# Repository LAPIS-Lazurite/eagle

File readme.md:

# notice of usage
this repository is for eagle library and SCH/PCB of Lazurite mini series.
Currently all files are not confirmed yet because PCB is under development. Please use it with your confirmation.

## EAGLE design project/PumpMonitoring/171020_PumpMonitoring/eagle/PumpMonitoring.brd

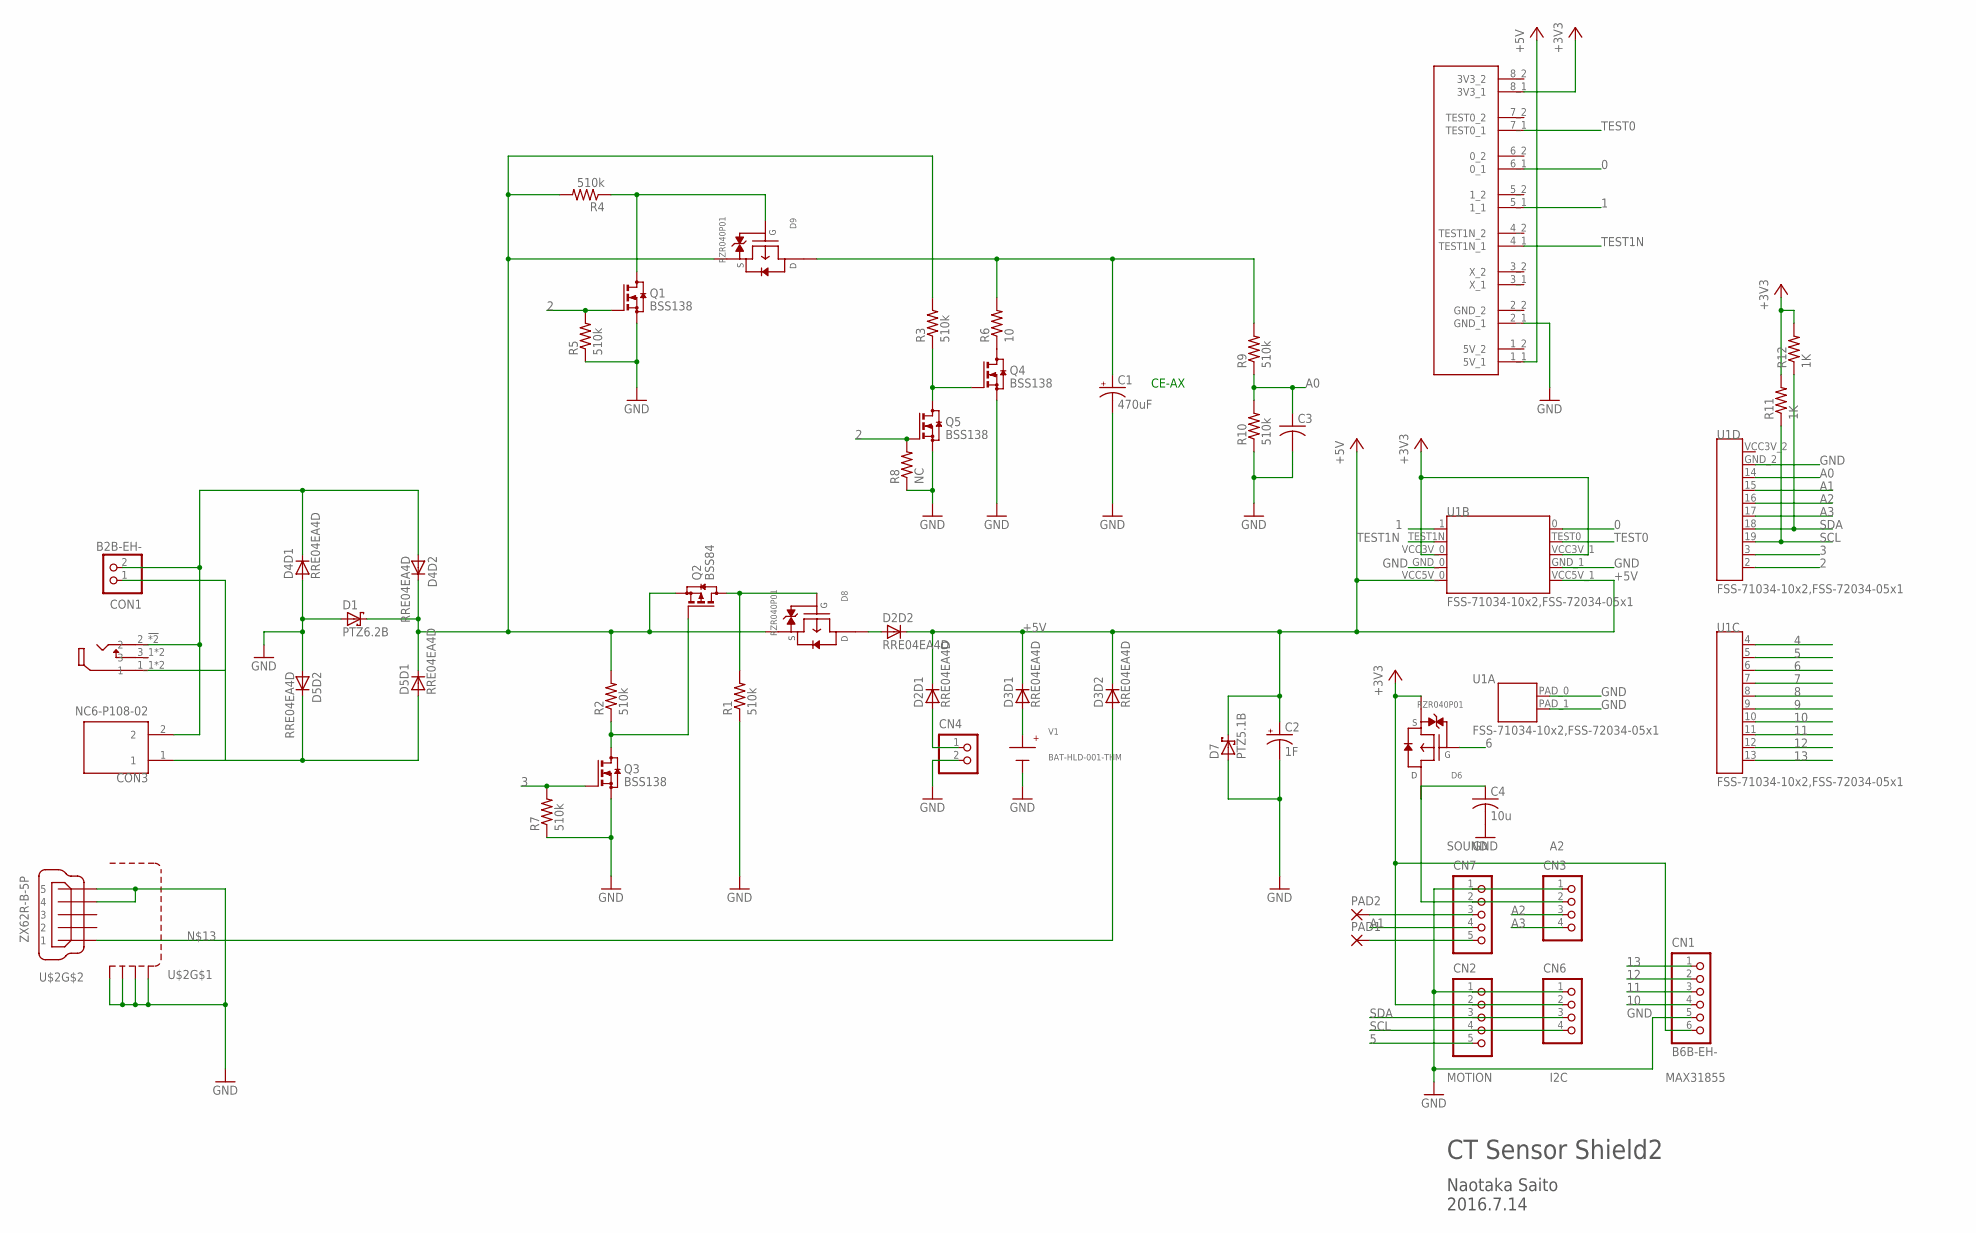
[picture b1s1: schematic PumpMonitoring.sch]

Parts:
C1: 470uF; E5-10,5
C2: 1F; E5-20
C3: C-USC0603; C0603
C4: 10u; C1206
CN1: B6B-EH-; B6B-EH
CN2, CN7: B5B-PH-K-S
CN3, CN6: B4B-PH-K-S
CN4: B2B-PH-K-S
CON1: B2B-EH-; B2B-EH
CON2: MJ-3536N
CON3: NC6-P108-02; 2PIN
D1: PTZ6.2B; DO214AC
D2, D3, D4, D5: RRE04EA4D; TSMD5
D6, D8, D9: RZR040P01; TSMT3
D7: PTZ5.1B; DO214AC
PAD1, PAD2: 1,6/0,9
Q1, Q3, Q4, Q5: BSS138; SOT23
Q2: BSS84; SOT23
R1, R2, R3, R4, R5, R7, R9, R10: 510k; R0603
R6: 10; EZP
R8: NC; R0603
R11, R12: 1K; R0603
U1: FSS-71034-10x2,FSS-72034-05x1; LAZURITE920J
U$1: XB-1-X
U$2: ZX62R-B-5P
V1: BAT-HLD-001-THM; CR2032

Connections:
0: U1.0, U$1.6_1 (0_1)
1: U1.1, U$1.5_1 (1_1)
2: Q1.1 (G), Q5.1 (G), R5.2, R8.2, U1.2
3: Q3.1 (G), R7.2, U1.3
4: U1.4
5: CN2.5, U1.5
6: D6.1 (G), U1.6
7: U1.7
8: U1.8
9: U1.9
10: CN1.4, U1.10
11: CN1.3, U1.11
12: CN1.2, U1.12
13: CN1.1, U1.13
+3V3: CN1.6, CN2.2, CN6.2, D6.2 (S), R11.2, R12.2, U1.VCC3V_0, U1.VCC3V_1, U$1.8_1 (3V3_1)
+5V: C2.+, D2.4 (C), D2.5 (C), D3.4 (C), D3.5 (C), D7.C, U1.VCC5V_0, U1.VCC5V_1, U$1.1_1 (5V_1)
A0: C3.1, R9.1, R10.2, U1.14
A1: CN7.4, U1.15
A2: CN3.3, U1.16
A3: CN3.4, U1.17
GND: C1.-, C2.-, C3.2, C4.2, CN1.5, CN2.1, CN3.1, CN4.2, CN6.1, CN7.1, D1.A, D4.1 (A), D5.3 (A), D7.A, Q1.2 (S), Q3.2 (S), Q4.2 (S), Q5.2 (S), R1.1, R5.1, R7.1, R8.1, R10.1, U1.GND_0, U1.GND_1, U1.GND_2, U1.PAD_0, U1.PAD_1, U$1.2_1 (GND_1), U$2.4, U$2.5, U$2.M1 (S1), U$2.M2 (S2), U$2.M3 (S3), U$2.M4 (S4), V1.GND
I+: CON1.2, CON2.2_2 (2), CON2.2_! (2), CON3.2, D4.3 (A), D4.5 (C)
I-: CON1.1, CON2.1_1 (1), CON2.1_2 (1), CON3.1, D5.1 (A), D5.4 (C)
IOUT: D1.C, D4.4 (C), D5.5 (C), D8.2 (S), D9.2 (S), Q2.2 (S), R2.2, R3.2, R4.2
unnamed: D8.1 (G), Q2.3 (D), R1.2
unnamed: D3.1 (A), V1.VDD1 (VDD), V1.VDD2 (VDD), V1.VDD3 (VDD), V1.VDD4 (VDD)
unnamed: CN4.1, D2.1 (A)
unnamed: C4.1, CN3.2, CN7.2, D6.3 (D)
unnamed: Q2.1 (G), Q3.3 (D), R2.1
unnamed: CN7.5, PAD1.1
unnamed: D9.1 (G), Q1.3 (D), R4.1
unnamed: CN7.3, PAD2.1
unnamed: Q4.3 (D), R6.1
unnamed: C1.+, D9.3 (D), R6.2, R9.2
unnamed: Q4.1 (G), Q5.3 (D), R3.1
unnamed: D2.3 (A), D8.3 (D)
unnamed: D3.3 (A), U$2.1
SCL: CN2.4, CN6.4, R11.1, U1.19
SDA: CN2.3, CN6.3, R12.1, U1.18
TEST0: U1.TEST0, U$1.7_1 (TEST0_1)
TEST1N: U1.TEST1N, U$1.4_1 (TEST1N_1)

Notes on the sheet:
CE-AX
CT Sensor Shield2
Naotaka Saito 2016.7.14
MOTION
SOUND
I2C
MAX31855

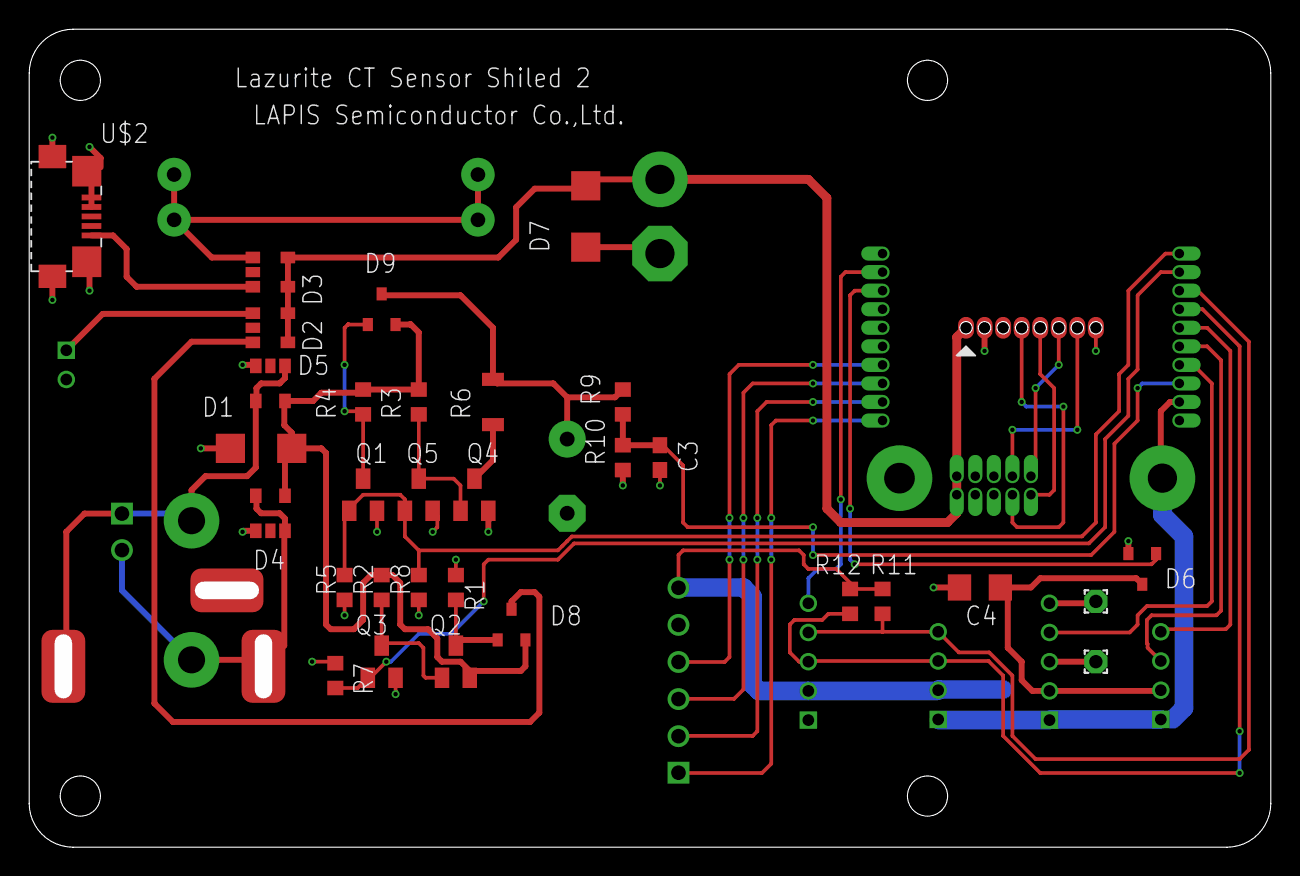
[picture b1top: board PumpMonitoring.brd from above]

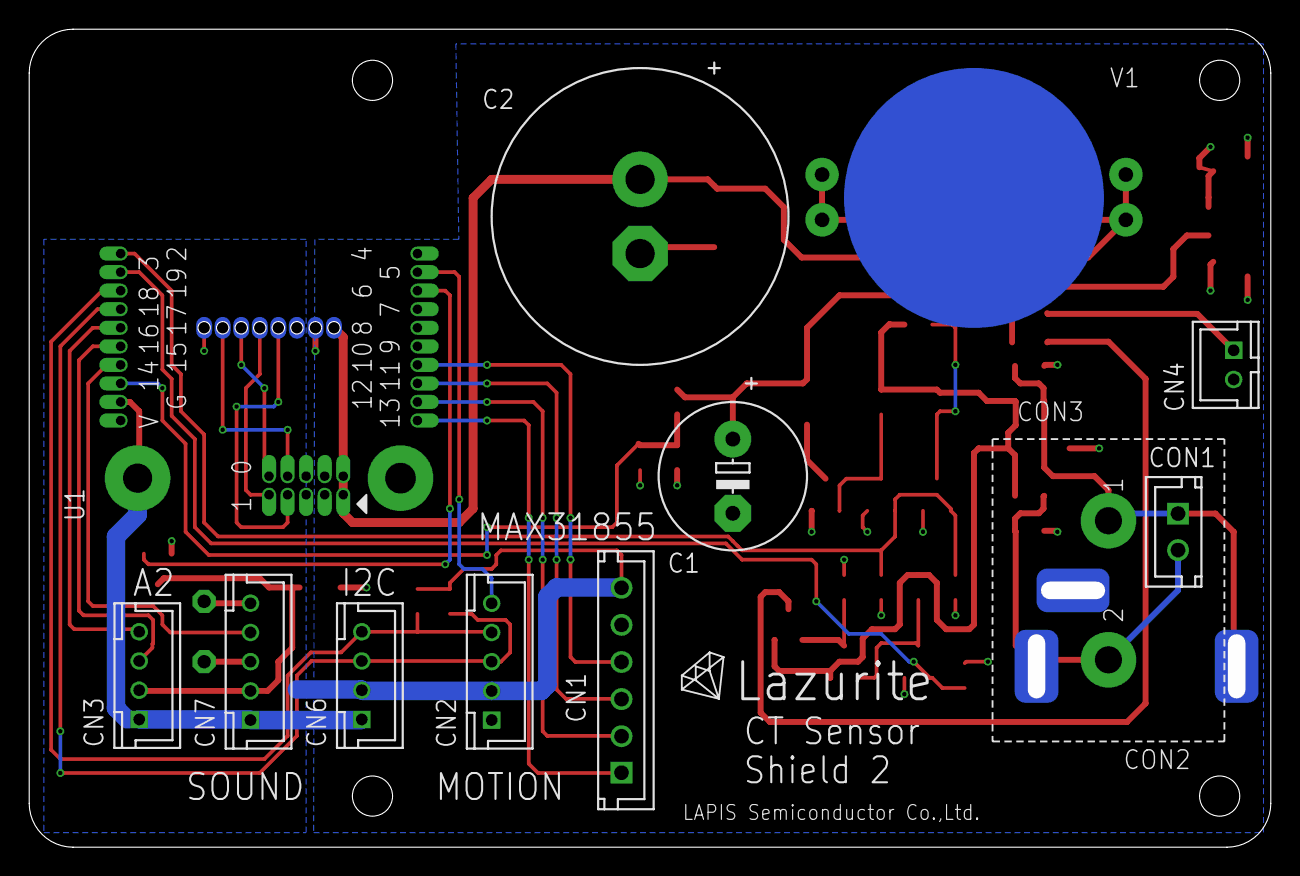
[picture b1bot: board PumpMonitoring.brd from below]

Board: 4 copper layers, 83.8 x 54.8 mm, 46 parts (14 on the bottom side), 37 nets.

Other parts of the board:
U$3: LOGO

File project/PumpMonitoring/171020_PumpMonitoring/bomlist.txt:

Partlist

Exported from PumpMonitoring.brd at 2017/10/20 9:58

EAGLE Version 7.6.0 Copyright (c) 1988-2016 CadSoft

Assembly variant: 

Part     Value                         Package      Library                 Position (mm)         Orientation

C1       470uF                         E5-10,5      rcl                     (36.83 25.4)          MR270
C2       1F                            E5-20        rcl                     (43.18 43.18)         MR270
C3                                     C0603        rcl                     (43.18 26.67)         R270
C4       10u                           C1206        rcl                     (65.0875 17.78)       R180
CN1      B6B-EH-                       B6B-EH       jst-ph                  (44.45 11.43)         MR90
CN2                                    B5B-PH-K-S   jst-ph                  (53.34 12.7)          MR90
CN3                                    B4B-PH-K-S   jst-ph                  (77.47 11.7475)       MR90
CN4                                    B2B-PH-K-S   jst-ph                  (2.54 33.02)          MR270
CN6                                    B4B-PH-K-S   jst-ph                  (62.23 11.7475)       MR90
CN7                                    B5B-PH-K-S   jst-ph                  (69.85 12.7)          MR90
CON1     B2B-EH-                       B2B-EH       jst-ph                  (6.35 21.59)          MR270
CON2     MJ-3536N                      MJ-3536N     mouser                  (7.9375 12.3825)      MR180
CON3     NC6-P108-02                   2PIN         lz-shield               (19.05 27.94)         MR270
D1       PTZ6.2B                       DO214AC      rohm2                   (15.875 27.305)       R0
D2       RRE04EA4D                     TSMD5        rohm2                   (16.51 35.56)         R270
D3       RRE04EA4D                     TSMD5        rohm2                   (16.51 39.37)         R270
D4       RRE04EA4D                     TSMD5        rohm2                   (16.51 22.86)         R0
D5       RRE04EA4D                     TSMD5        rohm2                   (16.51 31.75)         R180
D6       RZR040P01                     TSMT3        rohm2                   (76.2 19.05)          R180
D7       PTZ5.1B                       DO214AC      rohm2                   (38.1 43.18)          R90
D8       RZR040P01                     TSMT3        rohm2                   (33.02 15.24)         R0
D9       RZR040P01                     TSMT3        rohm2                   (24.13 36.83)         R0
PAD1                                   1,6/0,9      wirepad                 (73.025 16.8275)      R0
PAD2                                   1,6/0,9      wirepad                 (73.025 12.7)         R0
Q1       BSS138                        SOT23        transistor-small-signal (22.86 24.13)         R0
Q2       BSS84                         SOT23        transistor-small-signal (29.21 12.7)          R0
Q3       BSS138                        SOT23        transistor-small-signal (24.13 12.7)          R0
Q4       BSS138                        SOT23        transistor-small-signal (30.48 24.13)         R0
Q5       BSS138                        SOT23        transistor-small-signal (26.67 24.13)         R0
R1       510k                          R0603        resistor                (29.21 17.78)         R270
R2       510k                          R0603        resistor                (24.13 17.78)         R90
R3       510k                          R0603        resistor                (26.67 30.48)         R90
R4       510k                          R0603        resistor                (22.86 30.48)         R90
R5       510k                          R0603        resistor                (21.59 17.78)         R90
R6       10                            EZP          rohm2                   (31.75 30.48)         R90
R7       510k                          R0603        resistor                (20.955 11.7475)      R270
R8       NC                            R0603        resistor                (26.67 17.78)         R90
R9       510k                          R0603        resistor                (40.64 30.48)         R90
R10      510k                          R0603        resistor                (40.64 26.67)         R90
R11      1K                            R0603        resistor                (58.42 16.8275)       R90
R12      1K                            R0603        resistor                (56.1975 16.8275)     R90
U$1      XB-1-X                        XB-1-X       lz-shield               (67.945 35.56)        R180
U$2      ZX62R-B-5P                    ZX62R-B-5P   con-hirose              (1.5875 43.18)        R0
U1       FSS-71034-10x2,FSS-72034-05x1 LAZURITE920J lazurite                (63.5 24.13)          MR90
V1       BAT-HLD-001-THM               CR2032       mouser                  (20.32 44.45)         MR180

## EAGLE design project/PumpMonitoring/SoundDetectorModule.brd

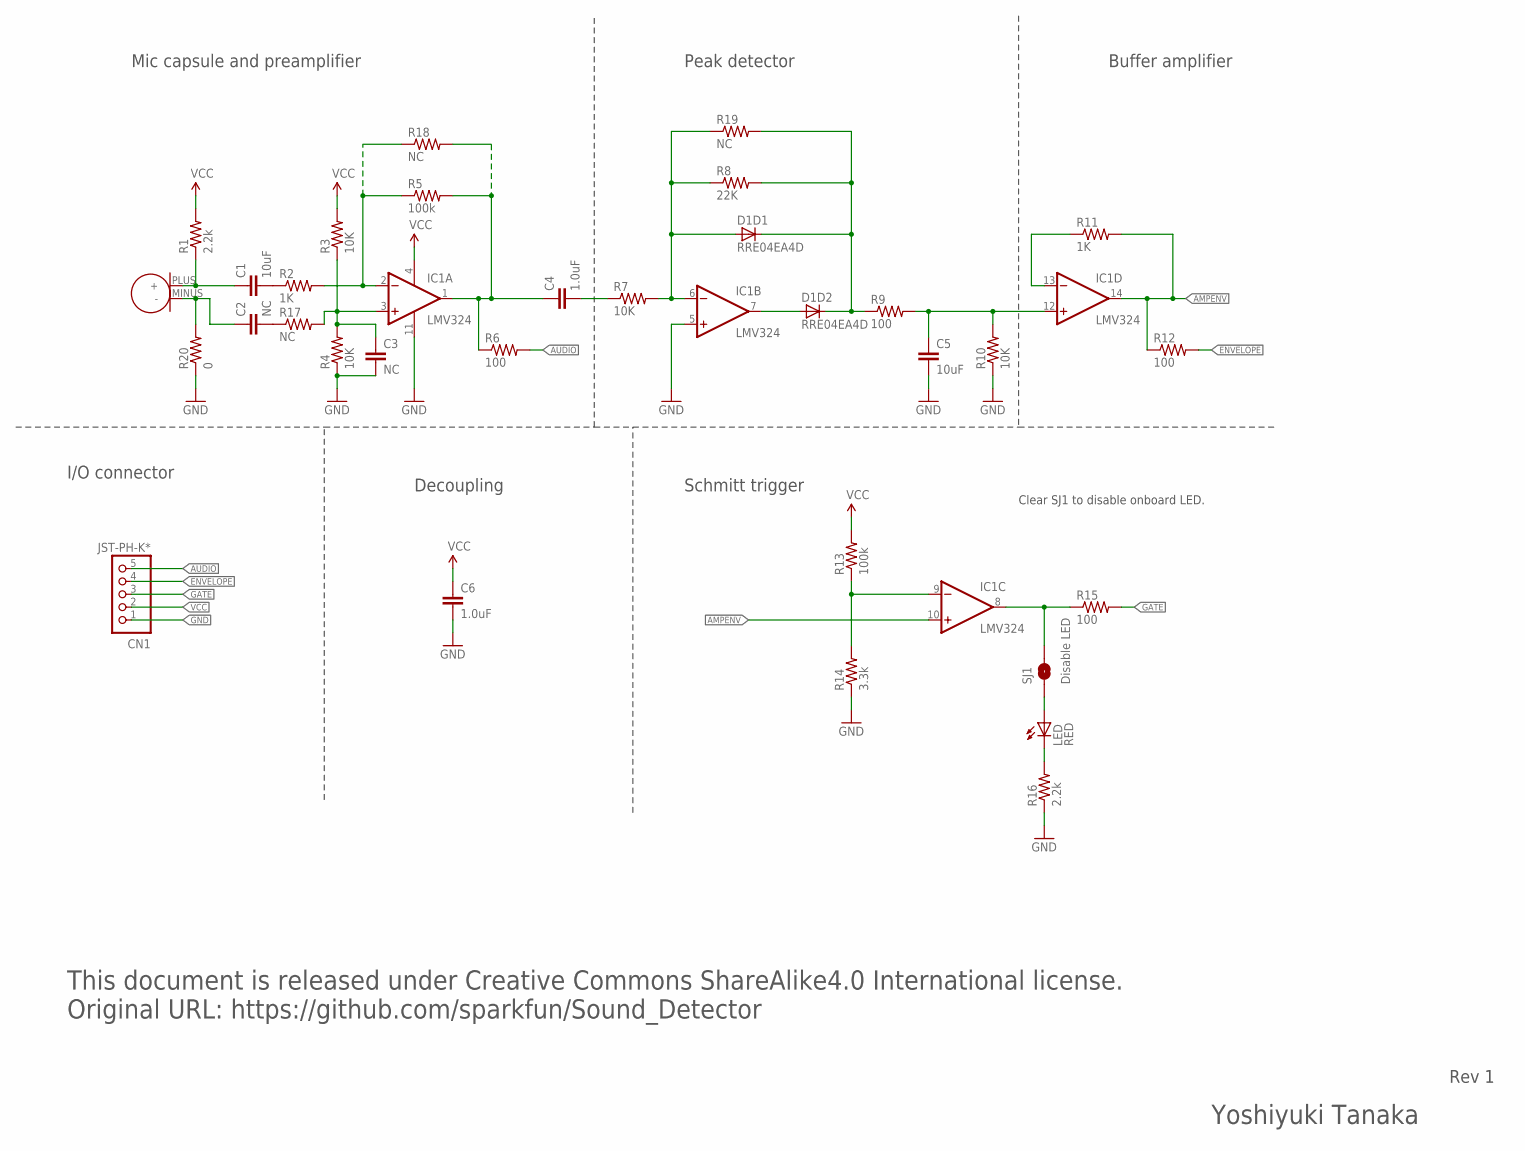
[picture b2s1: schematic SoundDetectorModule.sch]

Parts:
A1: MO093803-3
C1, C5: 10uF; C1206
C2, C3: NC; C0603
C4, C6: 1.0uF; C0603
CN1: JST-PH-K*; B5B-PH-SM4-TB
D1: RRE04EA4D; TSMD5
IC1: LMV324; SO14
LED: RED; SML-E1X
R1, R16: 2.2k; R0603
R2, R11: 1K; R0603
R3, R4, R7, R10: 10K; R0603
R5, R13: 100k; R0603
R6, R9, R12, R15: 100; R0603
R8: 22K; R0603
R14: 3.3k; R0603
R17: NC; R0603
R18, R19: NC; 0207/7
R20: 0; R0603
SJ1: Disable LED; SJ_2S

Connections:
AMPENV: IC1.10 (+IN), IC1.14 (OUT), R11.2, R12.1
AUDIO: CN1.5, R6.2
ENVELOPE: CN1.4, R12.2
GATE: CN1.3, R15.2
GND: C3.2, C5.2, C6.2, CN1.1, IC1.5 (+IN), IC1.11 (V-), R4.1, R10.1, R14.1, R16.1, R20.1
N$: C4.1, IC1.1 (OUT), R5.2, R6.1, R18.2
unnamed: A1.PLUS (+), C1.1, R1.1
unnamed: C3.1, IC1.3 (+IN), R3.1, R4.2, R17.2
unnamed: LED.C, R16.2
unnamed: IC1.2 (-IN), R2.2, R5.1, R18.1
unnamed: C1.2, R2.1
unnamed: C4.2, R7.1
unnamed: D1.1 (A), IC1.6 (-IN), R7.2, R8.1, R19.1
unnamed: D1.3 (A), IC1.7 (OUT)
unnamed: D1.4 (C), D1.5 (C), R8.2, R9.1, R19.2
unnamed: C5.1, IC1.12 (+IN), R9.2, R10.2
unnamed: IC1.13 (-IN), R11.1
unnamed: LED.A, SJ1.1
unnamed: C2.2, R17.1
unnamed: A1.MINUS (-), C2.1, R20.2
unnamed: IC1.9 (-IN), R13.1, R14.2
unnamed: IC1.8 (OUT), R15.1, SJ1.2
VCC: C6.1, CN1.2, IC1.4 (V+), R1.2, R3.2, R13.2

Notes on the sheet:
Mic capsule and preamplifier
Peak detector
Buffer amplifier
I/O connector
Decoupling
Schmitt trigger
Clear SJ1 to disable onboard LED.
Yoshiyuki Tanaka
Rev 1
This document is released under Creative Commons ShareAlike4.0 International license. Original URL: https://github.com/sparkfun/Sound_Detector

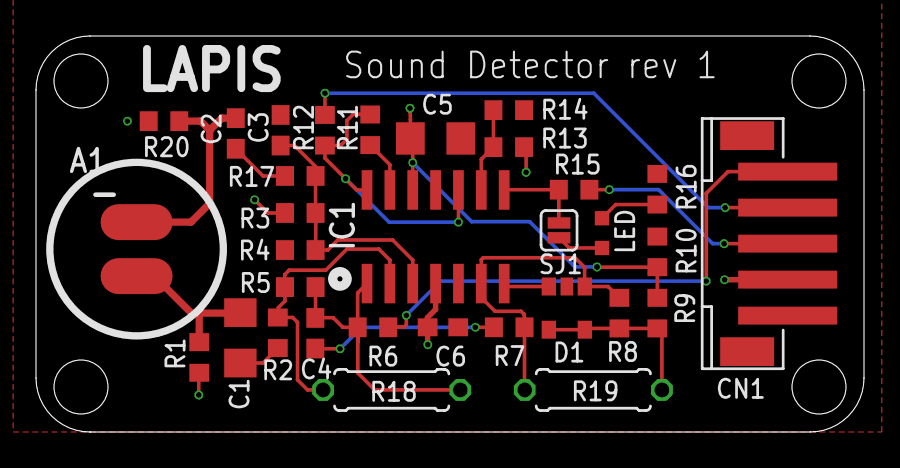
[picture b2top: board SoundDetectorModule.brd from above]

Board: 2 copper layers, 46.0 x 22.0 mm, 32 parts (0 on the bottom side), 23 nets.

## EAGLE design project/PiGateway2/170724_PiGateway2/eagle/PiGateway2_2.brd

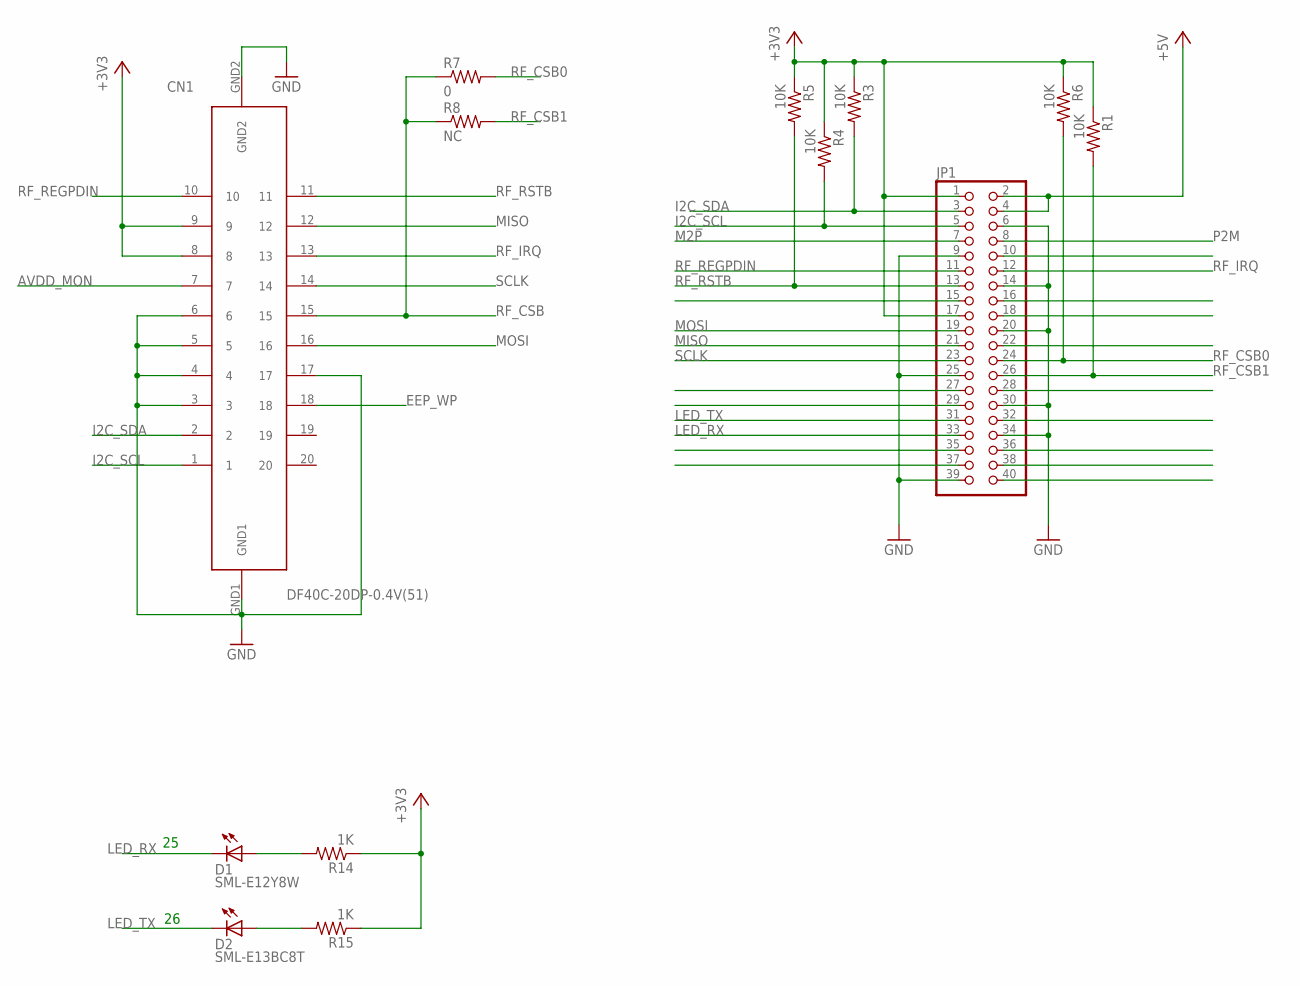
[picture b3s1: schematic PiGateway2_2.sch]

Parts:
CN1: DF40C-20DP-0.4V(51); BP3596A
D1: SML-E12Y8W; SML-E1X
D2: SML-E13BC8T; SML-E1X
JP1: PINHD-2X20; 2X20
R1, R3, R4, R5, R6: 10K; R0402
R7: 0; R0402
R8: NC; R0402
R14, R15: 1K; R0402

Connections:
+3V3: CN1.8, CN1.9, JP1.1, JP1.17, R1.1, R3.1, R4.1, R5.1, R6.1, R14.1, R15.1
+5V: JP1.2, JP1.4
AVDD_MON: CN1.7
EEP_WP: CN1.18
GND: CN1.3, CN1.4, CN1.5, CN1.6, CN1.17, CN1.GND1, CN1.GND2, JP1.6, JP1.9, JP1.14, JP1.20, JP1.25, JP1.30, JP1.34, JP1.39
I2C_SCL: CN1.1, JP1.5, R4.2
I2C_SDA: CN1.2, JP1.3, R3.2
LED_RX: D1.C, JP1.33
LED_TX: D2.C, JP1.31
M2P: JP1.7
MISO: CN1.12, JP1.21
MOSI: CN1.16, JP1.19
unnamed: D1.A, R14.2
unnamed: D2.A, R15.2
P2M: JP1.8
RF_CSB: CN1.15, R7.1, R8.1
RF_CSB0: JP1.24, R6.2, R7.2
RF_CSB1: JP1.26, R1.2, R8.2
RF_IRQ: CN1.13, JP1.12
RF_REGPDIN: CN1.10, JP1.11
RF_RSTB: CN1.11, JP1.13, R5.2
SCLK: CN1.14, JP1.23

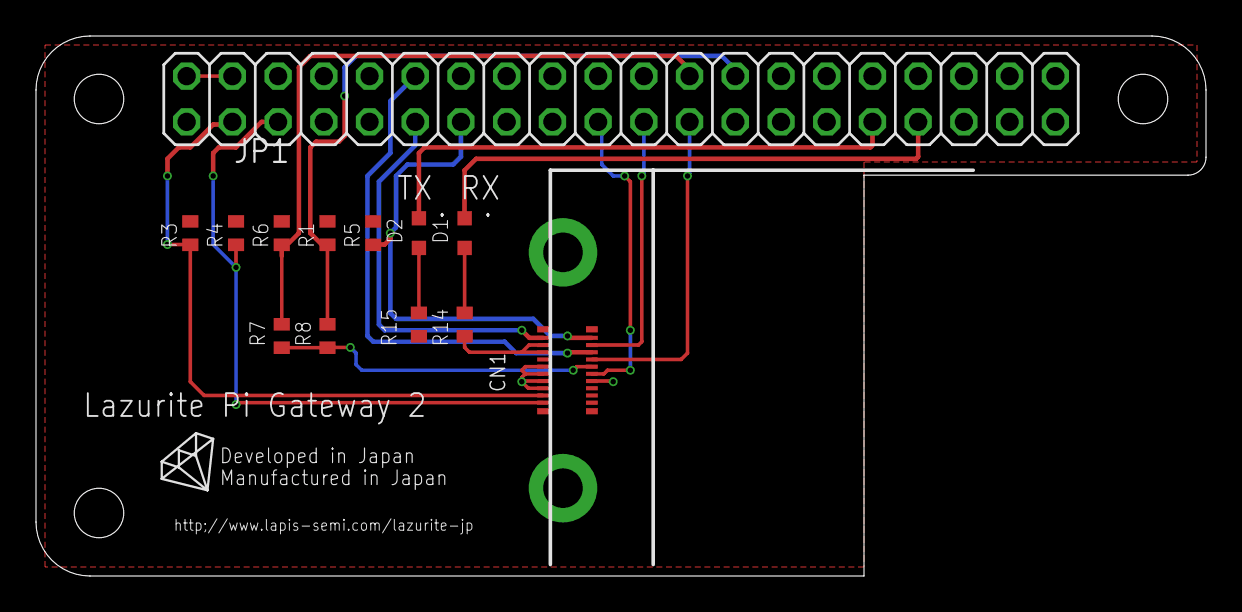
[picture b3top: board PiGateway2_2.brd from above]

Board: 2 copper layers, 65.0 x 30.0 mm, 14 parts (0 on the bottom side), 18 nets.

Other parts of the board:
U$1: LOGO

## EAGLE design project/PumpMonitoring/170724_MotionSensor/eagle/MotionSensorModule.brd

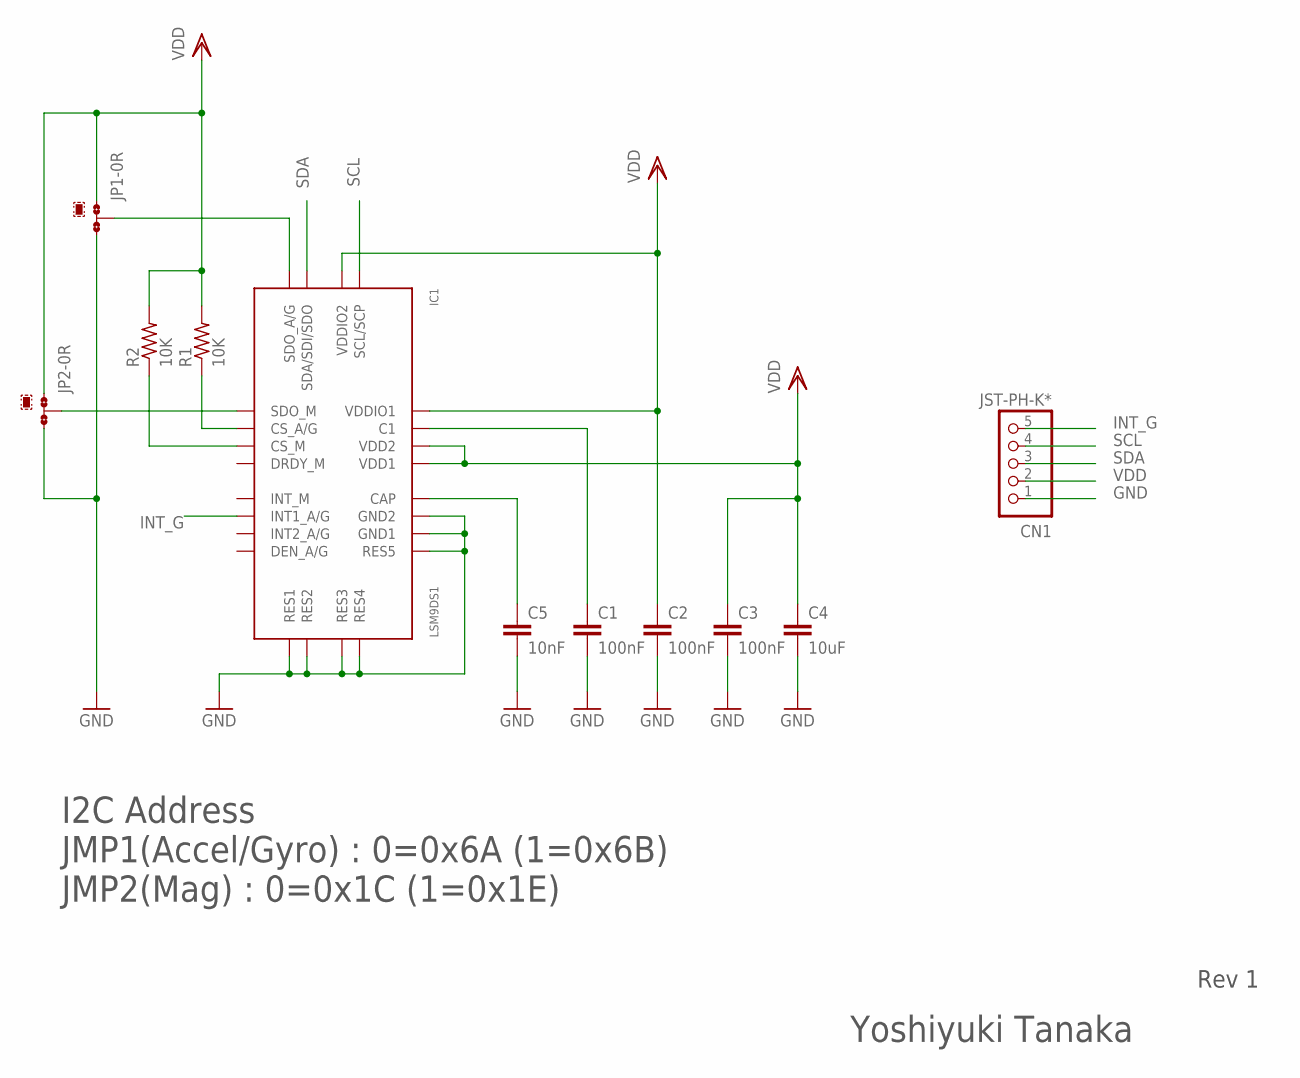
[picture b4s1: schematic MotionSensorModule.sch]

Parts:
C1, C2, C3: 100nF; C0603
C4: 10uF; C0603
C5: 10nF; C0603
CN1: JST-PH-K*; B5B-PH-SM4-TB
IC1: LSM9DS1; LGA-24L
JP1, JP2: 0R-JUMPB; B0R-JMP
R1, R2: 10K; R0603

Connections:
GND: C1.2, C2.2, C3.2, C4.2, C5.2, CN1.1, IC1.14 (RES1), IC1.15 (RES2), IC1.16 (RES3), IC1.17 (RES4), IC1.18 (RES5), IC1.19 (GND1), IC1.20 (GND2), JP1.3, JP2.3
INT_G: CN1.5, IC1.11 (INT1_A/G)
unnamed: C1.1, IC1.24 (C1)
unnamed: IC1.8 (CS_M), R2.1
unnamed: IC1.7 (CS_A/G), R1.1
unnamed: IC1.5 (SDO_A/G), JP1.2
unnamed: IC1.6 (SDO_M), JP2.2
unnamed: C5.1, IC1.21 (CAP)
SCL: CN1.4, IC1.2 (SCL/SCP)
SDA: CN1.3, IC1.4 (SDA/SDI/SDO)
VDD: C2.1, C3.1, C4.1, CN1.2, IC1.1 (VDDIO1), IC1.3 (VDDIO2), IC1.22 (VDD1), IC1.23 (VDD2), JP1.1, JP2.1, R1.2, R2.2

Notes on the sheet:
Yoshiyuki Tanaka
I2C Address JMP1(Accel/Gyro) : 0=0x6A (1=0x6B) JMP2(Mag) : 0=0x1C (1=0x1E)
Rev 1

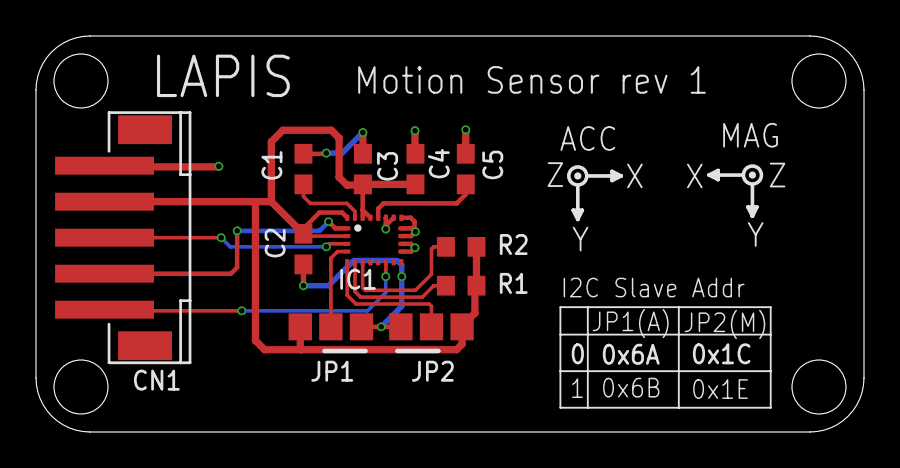
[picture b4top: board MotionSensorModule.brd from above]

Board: 2 copper layers, 46.0 x 22.0 mm, 11 parts (0 on the bottom side), 11 nets.

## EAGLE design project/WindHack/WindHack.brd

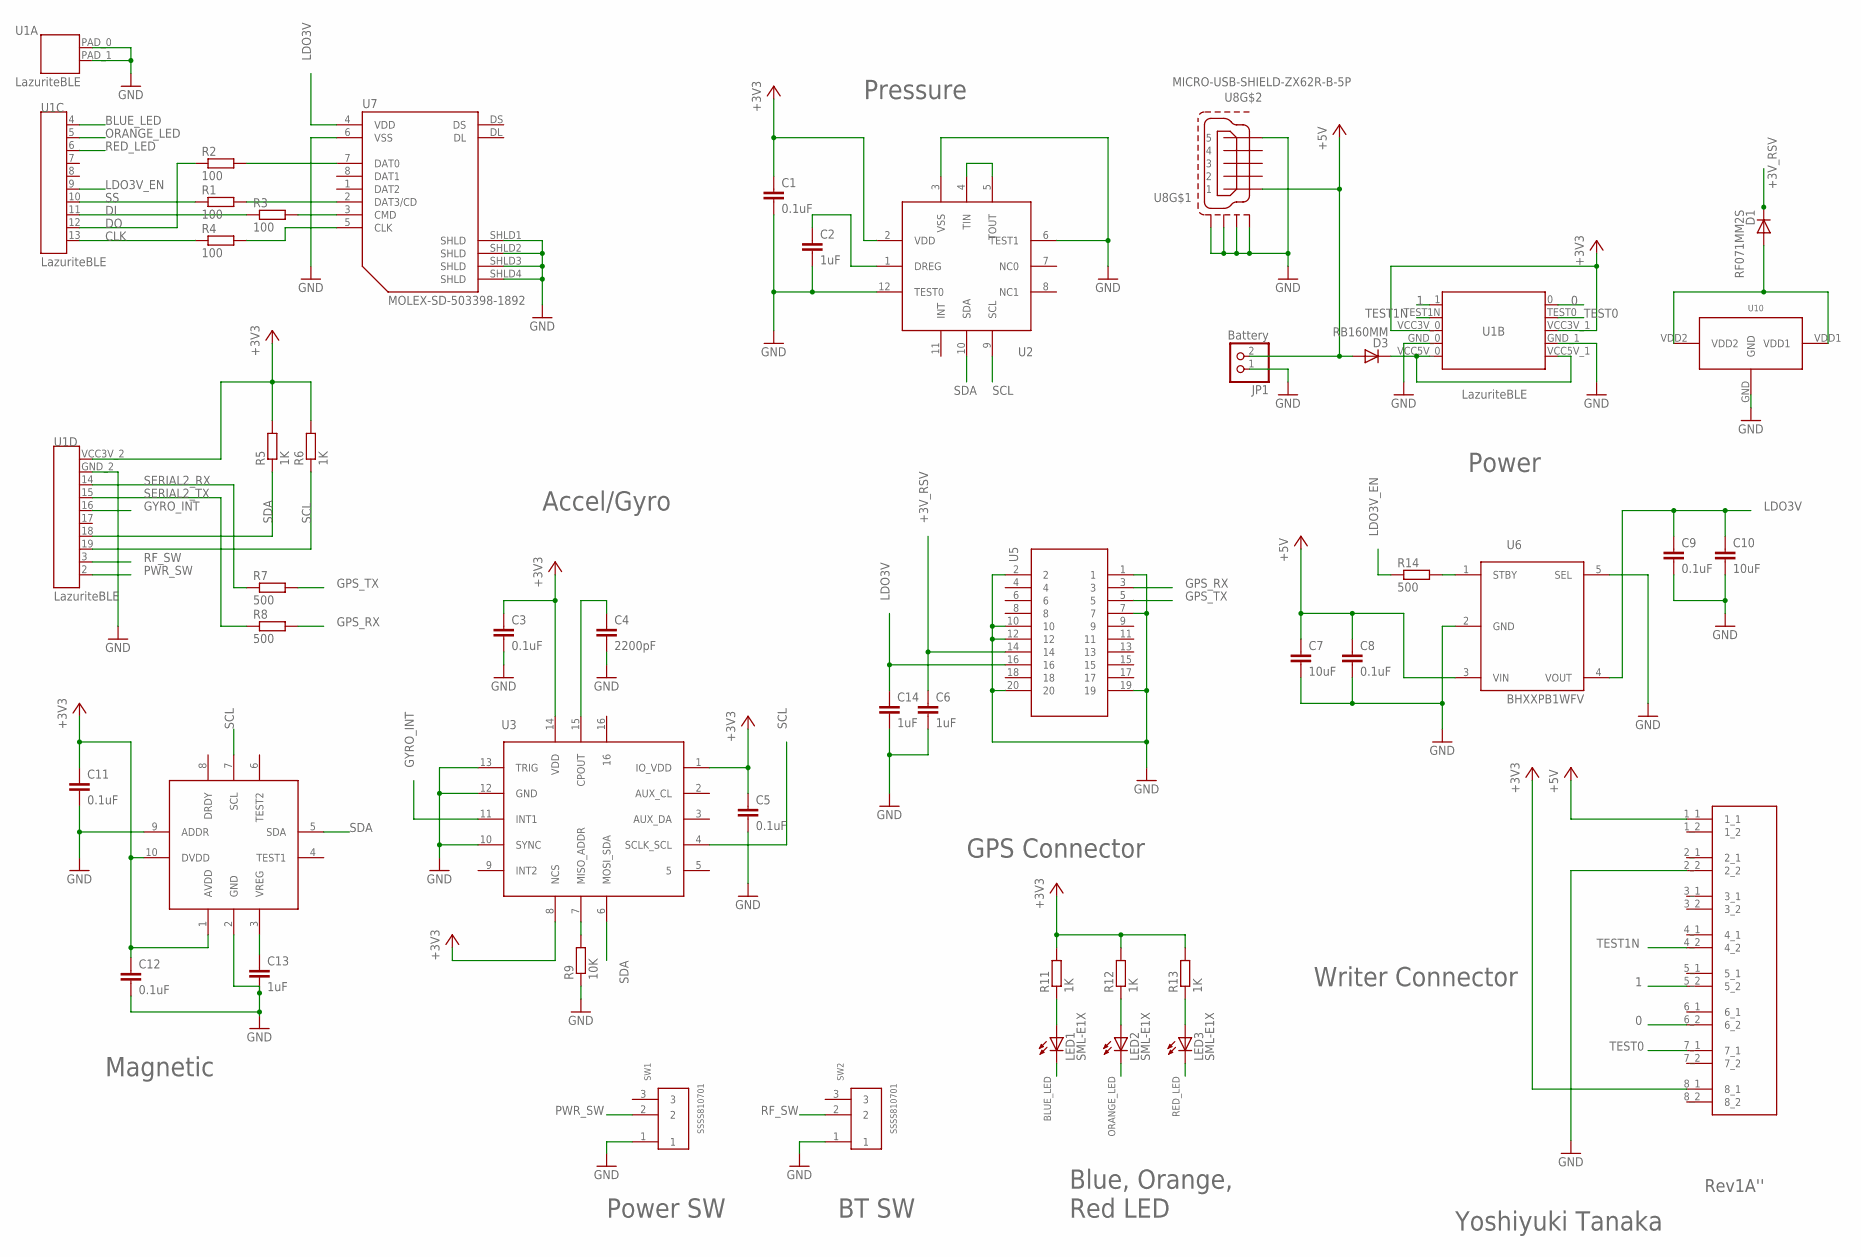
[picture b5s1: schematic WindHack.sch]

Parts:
C1, C3, C5, C8, C9, C11, C12: 0.1uF; C0603
C2, C6, C13, C14: 1uF; C0603
C4: 2200pF; C0603
C7, C10: 10uF; C0603
D1: RF071MM2S
D3: RB160MM; RB160MM-30
JP1: Battery; 1X02
LED1, LED2, LED3: SML-E1X
R1, R2, R3, R4: 100; R0603
R5, R6, R11, R12, R13: 1K; R0603
R7, R8, R14: 500; R0603
R9: 10K; R0603
SW1, SW2: SSSS810701
U1: LazuriteBLE; LAZURITE920J
U2: BM1383AGLV
U3: KXG03
U4: BM1422AGMV
U5: DF40C-20DS-0.4V
U6: BHXXPB1WFV; HVSOF5
U7: MOLEX-SD-503398-1892; MOLEX-SD-503398-003
U8: MICRO-USB-SHIELD-ZX62R-B-5P; ZX62R-B-5P
U10: BK-913
U$1: XB-1-X

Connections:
0: U1.0, U$1.6_2
1: U1.1, U$1.5_2
+3V3: C1.1, C3.1, C5.1, C11.1, C12.1, R5.2, R6.2, R11.2, R12.2, R13.2, U1.VCC3V_0, U1.VCC3V_1, U1.VCC3V_2, U2.2 (VDD), U3.1 (IO_VDD), U3.8 (NCS), U3.14 (VDD), U4.1 (AVDD), U4.10 (DVDD), U$1.8_1
+3V_RSV: C6.1, D1.C, U5.14
+5V: C7.1, C8.1, D3.A, JP1.2, U6.3 (VIN), U8.1, U$1.1_1
BLUE_LED: LED1.C, U1.4
CLK: R4.1, U1.13
DI: R3.1, U1.11
DO: R2.1, U1.12
GND: C1.2, C2.2, C3.2, C4.2, C5.2, C6.2, C7.2, C8.2, C9.2, C10.2, C11.2, C12.2, C13.2, C14.2, JP1.1, R9.1, SW1.1, SW2.1, U1.GND_0, U1.GND_1, U1.GND_2, U1.PAD_0, U1.PAD_1, U2.3 (VSS), U2.6 (TEST1), U2.12 (TEST0), U3.10 (SYNC), U3.12 (GND), U3.13 (TRIG), U4.2 (GND), U4.9 (ADDR), U5.1, U5.2, U5.7, U5.10, U5.12, U5.19, U5.20, U6.2 (GND), U6.5 (SEL), U7.6 (VSS), U7.SHLD1 (SHLD), U7.SHLD2 (SHLD), U7.SHLD3 (SHLD), U7.SHLD4 (SHLD), U8.5, U8.M1 (S1), U8.M2 (S2), U8.M3 (S3), U8.M4 (S4), U10.GND, U$1.2_2
GPS_RX: R8.2, U5.3
GPS_TX: R7.2, U5.5
GYRO_INT: U1.16, U3.11 (INT1)
LDO3V: C9.1, C10.1, C14.1, U5.16, U6.4 (VOUT), U7.4 (VDD)
LDO3V_EN: R14.1, U1.9
unnamed: LED1.A, R11.1
unnamed: LED2.A, R12.1
unnamed: U2.4 (TIN), U2.5 (TOUT)
unnamed: LED3.A, R13.1
unnamed: R9.2, U3.7 (MISO_ADDR)
unnamed: R14.2, U6.1 (STBY)
unnamed: C2.1, U2.1 (DREG)
unnamed: D1.A, U10.VDD1, U10.VDD2
unnamed: D3.C, U1.VCC5V_0, U1.VCC5V_1
unnamed: C13.1, U4.3 (VREG)
unnamed: C4.1, U3.15 (CPOUT)
ORANGE_LED: LED2.C, U1.5
PWR_SW: SW1.2, U1.2
RED_LED: LED3.C, U1.6
RF_SW: SW2.2, U1.3
SCL: R6.1, U1.19, U2.9 (SCL), U3.4 (SCLK_SCL), U4.7 (SCL)
SDA: R5.1, U1.18, U2.10 (SDA), U3.6 (MOSI_SDA), U4.5 (SDA)
SD_CLK: R4.2, U7.5 (CLK)
SD_DI: R3.2, U7.3 (CMD)
SD_DO: R2.2, U7.7 (DAT0)
SD_SS: R1.2, U7.2 (DAT3/CD)
SERIAL2_RX: R7.1, U1.14
SERIAL2_TX: R8.1, U1.15
SS: R1.1, U1.10
TEST0: U1.TEST0, U$1.7_1
TEST1N: U1.TEST1N, U$1.4_2

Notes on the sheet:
GPS Connector
Blue, Orange, Red LED
Accel/Gyro
Power
Pressure
Writer Connector
Magnetic
Power SW
BT SW
Yoshiyuki Tanaka
Rev1A''

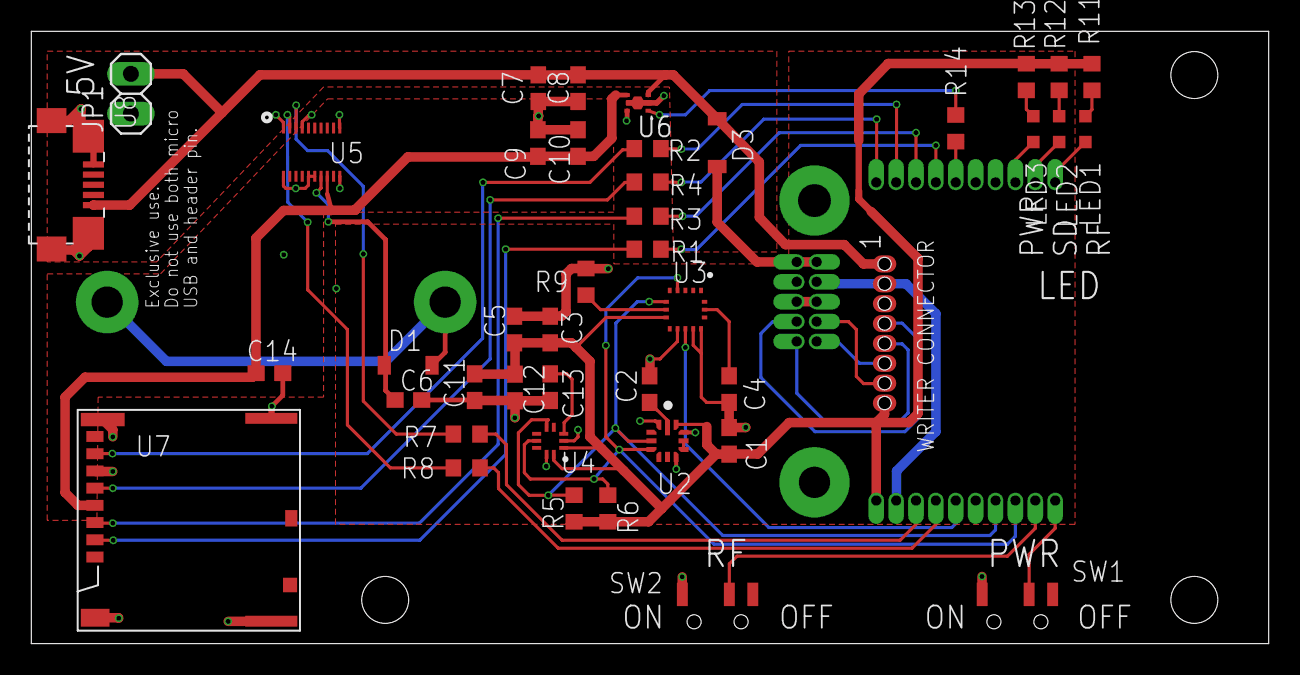
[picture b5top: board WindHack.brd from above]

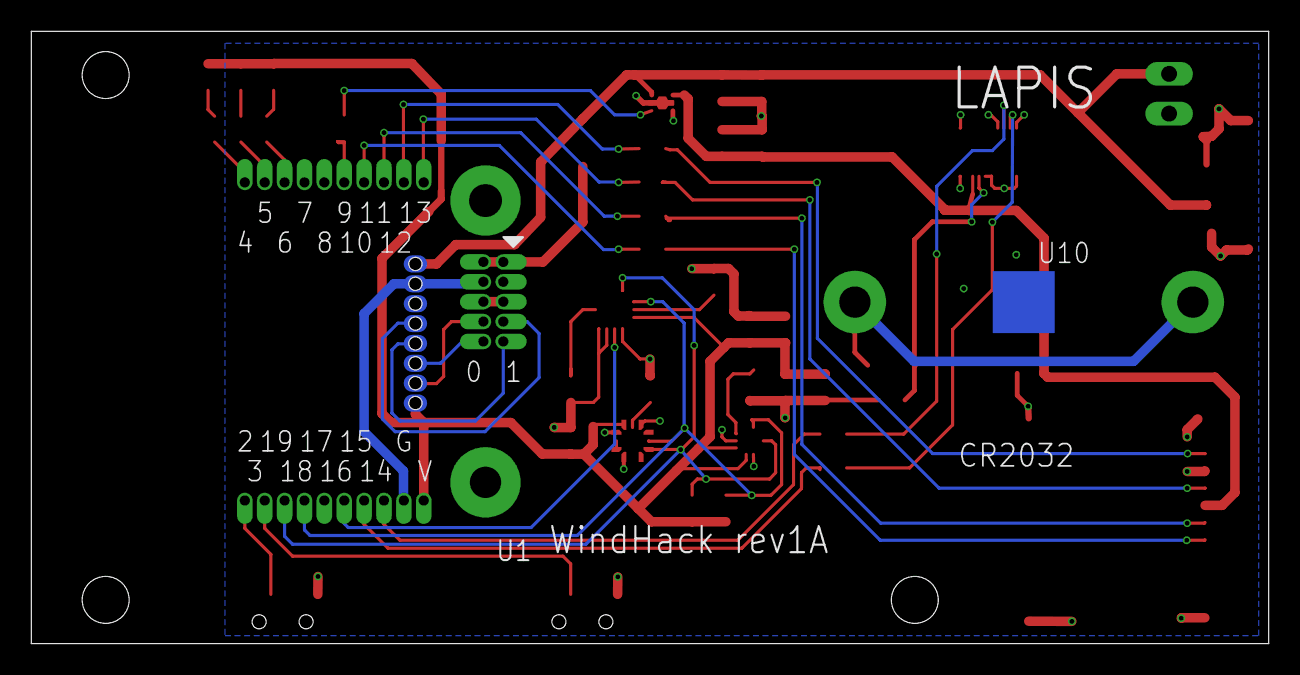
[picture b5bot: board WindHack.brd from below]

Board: 2 copper layers, 79.0 x 39.1 mm, 45 parts (2 on the bottom side), 41 nets.

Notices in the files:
parts and their libraries:
SparkFun-Aesthetics: Licensing: CC v3.0 Share-Alike You are welcome to use this library for commercial purposes.
